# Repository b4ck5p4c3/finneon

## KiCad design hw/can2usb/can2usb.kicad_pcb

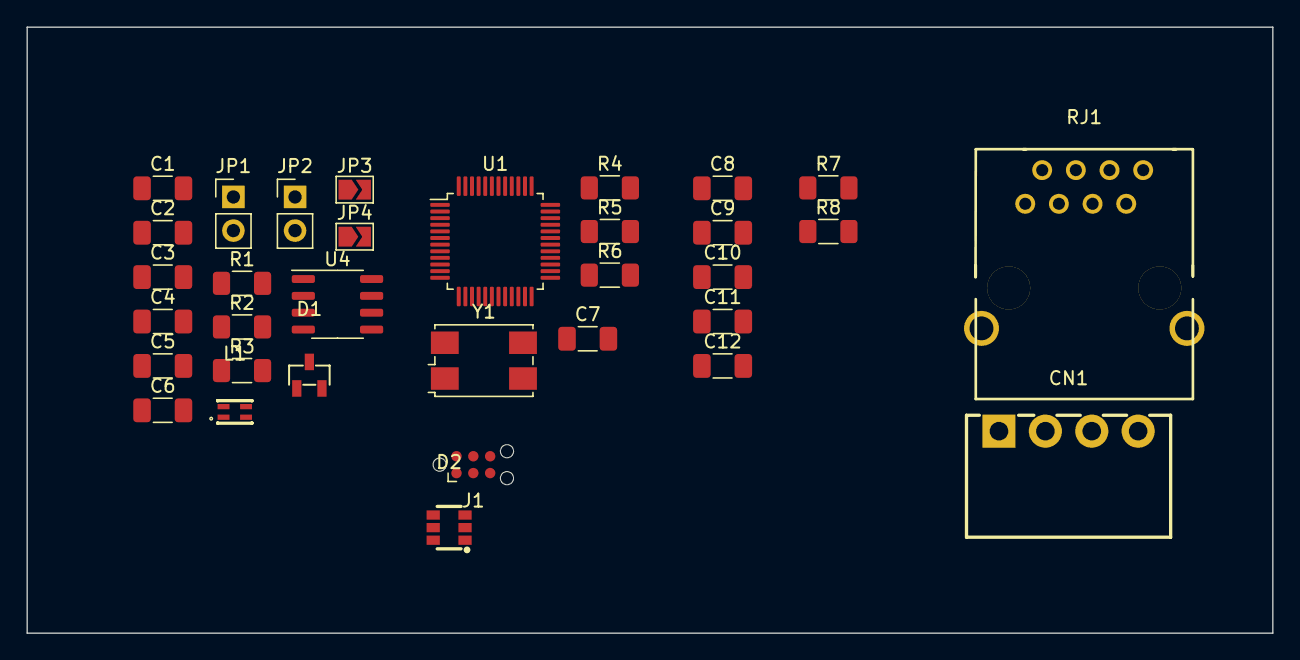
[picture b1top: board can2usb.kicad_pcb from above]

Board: 2 copper layers, 94.0 x 45.7 mm, 33 parts (0 on the bottom side), 21 nets, no tracks yet.

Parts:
C1, C2, C4, C5: 100pF 50V; C_1206_3216Metric_Pad1.33x1.80mm_HandSolder
C3: 4n7 100V; C_1206_3216Metric_Pad1.33x1.80mm_HandSolder
C6: 100nF 10V; C_1206_3216Metric_Pad1.33x1.80mm_HandSolder
C7, C10, C11, C12: 100n 10V; C_1206_3216Metric_Pad1.33x1.80mm_HandSolder
C8, C9: 20p 10V; C_1206_3216Metric_Pad1.33x1.80mm_HandSolder
CN1: 1844236; CONN-TH_1844236
D1: ESD2CAN24T2Q; SOT-23-3_L2.9-W1.3-P1.90-LS2.4-BL-1
D2: IP4220CZ6; TSOP-6_L3.0-W1.5-P0.95-LS2.8-BR
J1: TC2030-NL; Tag-Connect_TC2030-IDC-NL_2x03_P1.27mm_Vertical
JP1, JP2: Jumper; PinHeader_1x02_P2.54mm_Vertical
JP3, JP4: Jumper; SolderJumper-2_P1.3mm_Open_TrianglePad1.0x1.5mm
L1: DLW21HN900SQ2L; FILTER-SMD_4P-L2.0-W1.3-BL_DLW21
R1, R2: 60R; R_1206_3216Metric_Pad1.30x1.75mm_HandSolder
R3: 1K2R; R_1206_3216Metric_Pad1.30x1.75mm_HandSolder
R4, R5, R6, R7, R8: 10K; R_1206_3216Metric_Pad1.30x1.75mm_HandSolder
RJ1: DS1125; RJ45-TH_DS1127-S80BP
U1: STM32F103CBT6; LQFP-48_7x7mm_P0.5mm
U4: PCA82C250; SO-8_3.9x4.9mm_P1.27mm
Y1: 8 MHz; Crystal_SMD_7050-4Pin_7.0x5.0mm

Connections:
8P_VIN: RJ1.4, RJ1.5, RJ1.8
+5V: C6.1, U4.3 (VCC)
/CAN/CAN_HI: C5.1, D1.2, JP2.2 (B), JP4.2 (B), L1.1
/CAN/CAN_LO: C4.1, D1.1, JP1.1 (A), JP3.1 (A), L1.4
BOOT0: R6.2, U1.44 (BOOT0)
BOOT1: R5.2, U1.20 (PB2)
Earth: RJ1.0, RJ1.6
GND: C1.2, C2.2, C3.1, C4.2, C5.2, C6.2, C7.2, C8.2, C9.2, C10.2, C11.2, C12.2, D1.3, D2.2 (GND), J1.5 (GND), R3.2, R5.1, R6.1, R8.1, RJ1.3, RJ1.7, U1.8 (VSSA), U1.23 (VSS), U1.35 (VSS), U1.47 (VSS), U4.2 (GND)
NRST: C7.1, D2.6 (I/O4), J1.3 (~RESET), R4.2, U1.7 (NRST)
unnamed: C3.2, R1.2, R2.1
unnamed: JP1.2 (B), JP3.2 (B), R2.2
unnamed: JP2.1 (A), JP4.1 (A), R1.1
unnamed: C2.1, L1.2, U4.7 (CAN+)
unnamed: C1.1, L1.3, U4.6 (CAN-)
unnamed: R3.1, U4.8 (Rsl)
OSCIN: C9.1, U1.6 (PD1), Y1.1
OSCOUT: C8.1, U1.5 (PD0), Y1.3
SWCLK: D2.4 (I/O3), J1.4 (SWCLK), R8.2, U1.37 (PA14)
SWDIO: D2.3 (I/O2), J1.2 (SWDIO), R7.2, U1.34 (PA13)
SWO: D2.1 (I/O1), J1.6 (SWO), U1.39 (PB3)
VBAT: C10.1, C11.1, C12.1, D2.5 (VCC), J1.1 (VCC), R4.1, R7.1, U1.1 (VBAT), U1.9 (VDDA), U1.24 (VDD), U1.36 (VDD), U1.48 (VDD)

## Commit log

2024-06-24 feat: old can2usb drafts
